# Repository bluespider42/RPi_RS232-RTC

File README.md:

Raspberry Pi RTC Serial and Power

Used KiCad Template from XESS Corp.
[link] (https://github.com/xesscorp/RPi_Hat_Template)

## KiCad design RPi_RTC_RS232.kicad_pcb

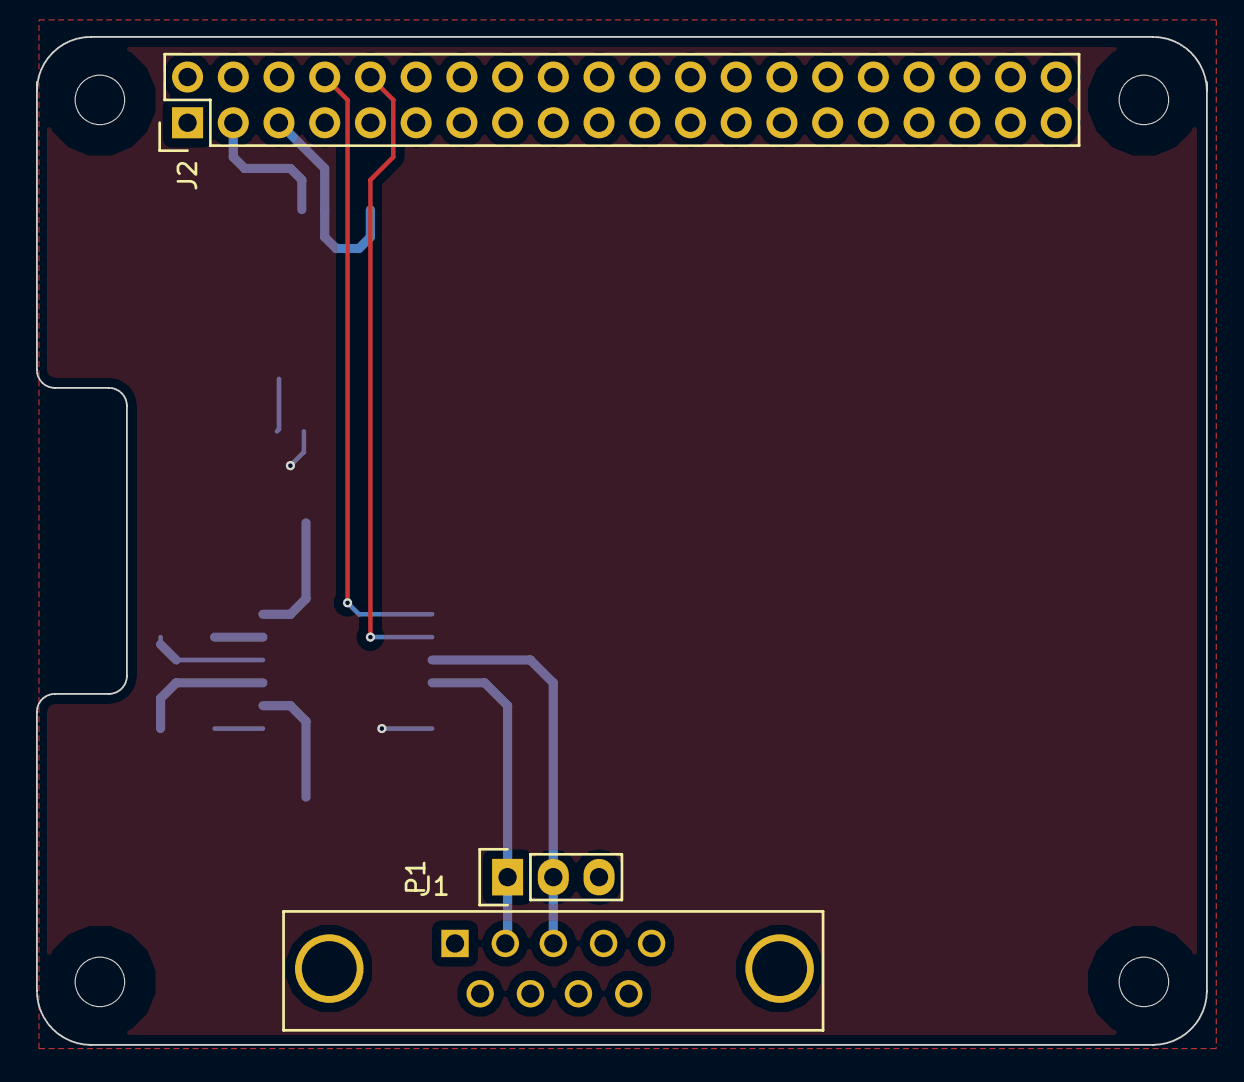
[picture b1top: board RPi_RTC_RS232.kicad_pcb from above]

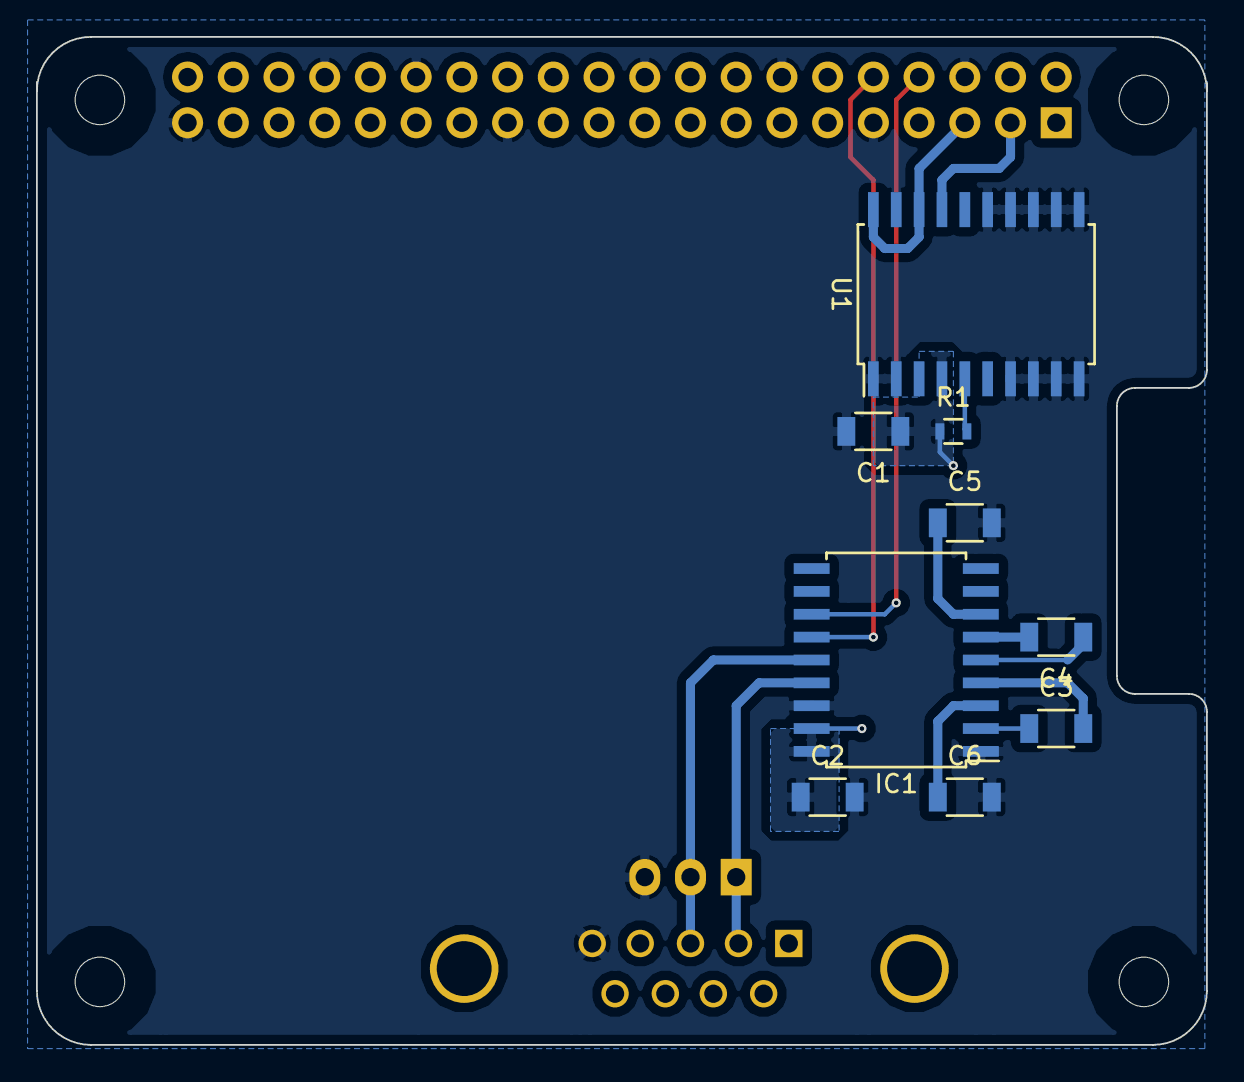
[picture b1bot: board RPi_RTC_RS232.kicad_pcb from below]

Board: 2 copper layers, 65.0 x 56.0 mm, 12 parts (9 on the bottom side), 17 nets.

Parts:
C1: 1uF; C_1206
C2, C3, C4, C5, C6: 0.1uF; C_1206
IC1: MAX3222; SOIC-18_7.5x11.6mm_Pitch1.27mm
J1: DB9; DB9MD
J2: RPi_GPIO; Pin_Header_Straight_2x20
P1: CONN_01X03; Pin_Header_Straight_1x03
R1: R; R_0603
U1: DS3232; SOIC-20_7.5x12.8mm_Pitch1.27mm

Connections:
+3.3VP: J2.1, J2.17
+5VP: J2.2, J2.4
/RPi_GPIO/SCL: J2.5, U1.18, U1.20
/RPi_GPIO/SDA: J2.3, U1.17
/RS232/RPi_R1: IC1.13, J2.10
/RS232/RPi_T1: IC1.12, J2.8
/RS232/RS232_R1: IC1.14, J1.3, P1.2
/RS232/RS232_T1: IC1.15, J1.2, P1.1
/RTC/SQW: R1.2, U1.5
GND: C1.2, C2.2, C5.2, C6.2, IC1.1, IC1.16, J1.5, J2.6, J2.9, J2.14, J2.20, J2.25, J2.30, J2.34, J2.39, P1.3, U1.1, U1.2, U1.7, U1.8, U1.9, U1.10, U1.11, U1.12, U1.13, U1.14, U1.15, U1.19
unnamed: C3.1, IC1.2
unnamed: C3.2, IC1.4
unnamed: C4.1, IC1.5
unnamed: C4.2, IC1.6
unnamed: C5.1, IC1.7
unnamed: C6.1, IC1.3
VCC: C1.1, C2.1, IC1.17, IC1.18, R1.1, U1.4

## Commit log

2015-05-19 schematic and provisional layout for RTC and RS232
2015-05-20 added power and nimh charge IC TODO charge circuit
2015-05-21 added relay based 5v power switch
